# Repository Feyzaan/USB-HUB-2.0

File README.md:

# GL850G + TPS2044B USB Hub — Validation Board

A self-powered, 4-port USB 2.0 hub PCB built to validate independent per-port power switching and fault isolation before use in a larger project. Each downstream port can be individually enabled, current-limited, and fault-reported — a short or overcurrent event on one port never affects the others.

## Overview

Most low-cost USB hubs share power switching across all ports in a single "gang" — one fault trips every port at once. This board is designed the other way: each port has its own dedicated enable and fault-report line, driven by a hub controller running in **individual power mode**, with the actual current-limiting handled by a separate quad power-distribution switch.

This board exists purely to validate that architecture in isolation — no other subsystems, no assumptions carried over from a datasheet reference circuit without independent verification.

## Key Features

- **Independent per-port power switching** — each of the 4 downstream ports has its own enable/fault signal pair, not a shared gang-mode circuit
- **Active overcurrent protection** — a fault on one port trips only that port's power channel; the remaining ports continue operating normally
- **Self-powered architecture** — the hub sources its own downstream power rather than drawing everything from the host's USB port budget
- **Reverse-current protection** — a P-channel MOSFET on the USB-C input blocks the board's local supply from backfeeding into the host
- **USB Type-C current advertisement** — CC-line resistors advertise 1.5 A to the host instead of the USB 2.0 default of 500 mA, using passive resistors only (no PD controller)
- **Per-port status indication** — dual-color LEDs report each port's connection/fault state
- **Independent, isolated crystal oscillators** — the hub controller and any downstream logic run on separate, dedicated clock sources

## Hardware

| Function | Part |
|---|---|
| USB hub controller | Genesys Logic GL850G-MNG21 (LQFP48, individual power mode) |
| Power distribution switch | Texas Instruments TPS2044BDR (quad, independently current-limited channels) |
| Reverse-current blocking | SI2301 P-channel MOSFET |
| Host connector | USB-C (16-pin, reversible) |
| Downstream connectors | 4× USB-A |
| Status indication | Dual-color (green/amber) LEDs, one per port |

## Design Notes

- The hub controller's power-on strap pins configure port count, power-switch polarity, and per-port removable/non-removable status; several of these pins double as status-LED drivers after the strap window closes, requiring careful resistor sizing so the two functions don't interfere with each other.
- Overcurrent-report lines are open-drain and require external pull-ups — this is easy to miss if relying on a symbol's default connections rather than the manufacturer's application circuit.
- Reset sensing is derived from the raw, upstream USB VBUS rail (ahead of the reverse-blocking MOSFET) rather than the board's own regulated rail, so a cable disconnect is detected immediately rather than after the local bulk capacitance discharges.

## Status

Schematic complete and cross-checked pin-by-pin against manufacturer datasheets. PCB fabrication in progress.

## Gallery

**3D render**

**Copper layers**

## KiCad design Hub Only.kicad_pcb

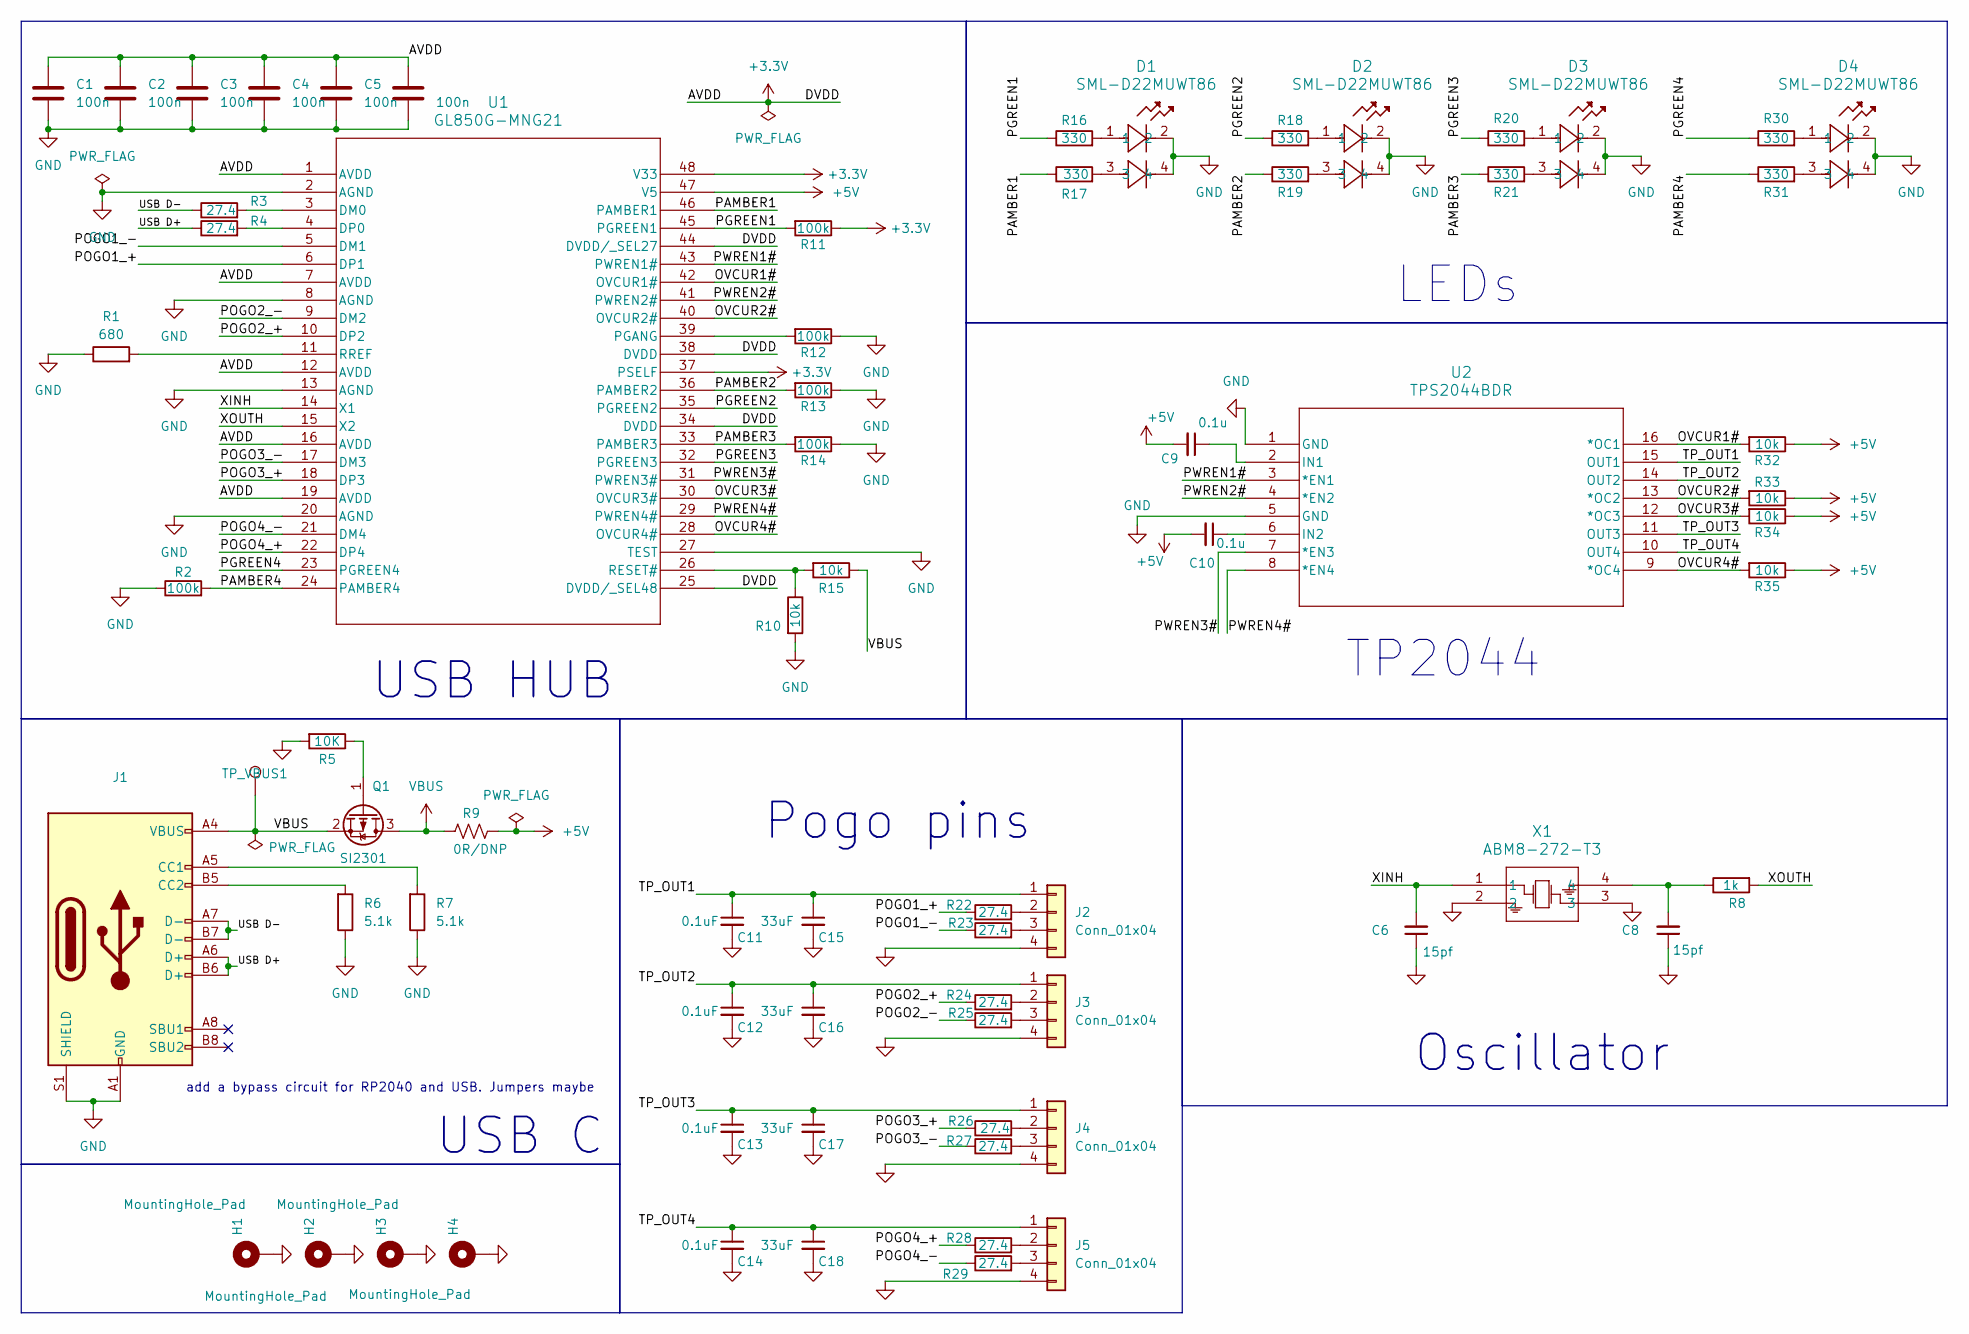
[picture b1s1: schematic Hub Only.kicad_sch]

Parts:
C1, C2, C3, C4, C5, C7: 100n; C_0603_1608Metric
C6, C8: 15pf; C_0603_1608Metric
C9, C10: 0.1u; C_0603_1608Metric
C11, C12, C13, C14: 0.1uF; C_0603_1608Metric
C15, C16, C17, C18: 33uF; C_0603_1608Metric
D1, D2, D3, D4: SML-D22MUWT86; LED_SML-D22_ROM
H1, H2, H3, H4: MountingHole_Pad; MountingHole_2.2mm_M2_DIN965_Pad
J1: USB_C_Receptacle_XKB_U262-16XN-4BVC11
J2, J3, J4, J5: Conn_01x04; USB_A_Molex_67643_Horizontal
Q1: SI2301; SOT-23
R1: 680; R_0603_1608Metric_Pad0.98x0.95mm_HandSolder
R2, R11, R12, R13, R14: 100k; R_0603_1608Metric_Pad0.98x0.95mm_HandSolder
R3, R4, R22, R23, R24, R25, R26, R27, R28, R29: 27.4; R_0603_1608Metric_Pad0.98x0.95mm_HandSolder
R5: 10K; R_0603_1608Metric_Pad0.98x0.95mm_HandSolder
R6, R7: 5.1k; R_0603_1608Metric
R8: 1k; R_0603_1608Metric
R9: 0R/DNP; R_0603_1608Metric
R10, R15, R32, R33, R34, R35: 10k; R_0603_1608Metric_Pad0.98x0.95mm_HandSolder
R16, R17, R18, R19, R20, R21, R30, R31: 330; R_0603_1608Metric_Pad0.98x0.95mm_HandSolder
TP_VBUS1: TestPoint; TestPoint_Pad_D1.0mm
U1: GL850G-MNG21; QFN48_GL850G_7x7-0P5_GEN
U2: TPS2044BDR; D16
X1: ABM8-272-T3; ABM8-272-T3_ABR

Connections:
+3.3V: C1.2, C2.2, C3.2, C4.2, C5.2, C7.2, R11.1, U1.1 (AVDD), U1.7 (AVDD), U1.12 (AVDD), U1.16 (AVDD), U1.19 (AVDD), U1.25 (DVDD/_SEL48), U1.34 (DVDD), U1.37 (PSELF), U1.38 (DVDD), U1.44 (DVDD/_SEL27), U1.48 (V33)
+5V: C9.2, C10.2, R9.2, R32.1, R33.1, R34.1, R35.1, U1.47 (V5)
/OVCUR1#: R32.2, U1.42 (OVCUR1#), U2.16 (*OC1)
/OVCUR2#: R33.2, U1.40 (OVCUR2#), U2.13 (*OC2)
/OVCUR3#: R34.2, U1.30 (OVCUR3#), U2.12 (*OC3)
/OVCUR4#: R35.2, U1.28 (OVCUR4#), U2.9 (*OC4)
/PAMBER1: R17.1, U1.46 (PAMBER1)
/PAMBER2: R13.2, R19.1, U1.36 (PAMBER2)
/PAMBER3: R14.2, R21.1, U1.33 (PAMBER3)
/PAMBER4: R2.2, R31.1, U1.24 (PAMBER4)
/PGREEN1: R11.2, R16.1, U1.45 (PGREEN1)
/PGREEN2: R18.1, U1.35 (PGREEN2)
/PGREEN3: R20.1, U1.32 (PGREEN3)
/PGREEN4: R30.1, U1.23 (PGREEN4)
/POGO1_+: R22.1, U1.6 (DP1)
/POGO1_-: R23.1, U1.5 (DM1)
/POGO2_+: R24.1, U1.10 (DP2)
/POGO2_-: R25.1, U1.9 (DM2)
/POGO3_+: R26.1, U1.18 (DP3)
/POGO3_-: R27.1, U1.17 (DM3)
/POGO4_+: R28.1, U1.22 (DP4)
/POGO4_-: R29.1, U1.21 (DM4)
/PWREN1#: U1.43 (PWREN1#), U2.3 (*EN1)
/PWREN2#: U1.41 (PWREN2#), U2.4 (*EN2)
/PWREN3#: U1.31 (PWREN3#), U2.7 (*EN3)
/PWREN4#: U1.29 (PWREN4#), U2.8 (*EN4)
/TP_OUT1: C11.1, C15.1, J2.1, U2.15 (OUT1)
/TP_OUT2: C12.1, C16.1, J3.1, U2.14 (OUT2)
/TP_OUT3: C13.1, C17.1, J4.1, U2.11 (OUT3)
/TP_OUT4: C14.1, C18.1, J5.1, U2.10 (OUT4)
/USB D+: J1.A6 (D+), J1.B6 (D+), R4.1
/USB D-: J1.A7 (D-), J1.B7 (D-), R3.1
/XINH: C6.2, U1.14 (X1), X1.1
/XOUTH: R8.1, U1.15 (X2)
GND: C1.1, C2.1, C3.1, C4.1, C5.1, C6.1, C7.1, C8.1, C11.2, C12.2, C13.2, C14.2, C15.2, C16.2, C17.2, C18.2, D1.2, D1.4, D2.2, D2.4, D3.2, D3.4, D4.2, D4.4, H1.1, H2.1, H3.1, H4.1, J1.A1 (GND), J1.A12 (GND), J1.B1 (GND), J1.B12 (GND), J1.S1 (SHIELD), J2.4, J3.4, J4.4, J5.4, R1.1, R2.1, R5.2, R6.2, R7.2, R10.2, R12.1, R13.1, R14.1, U1.2 (AGND), U1.8 (AGND), U1.13 (AGND), U1.20 (AGND), U1.27 (TEST), U2.1 (GND), U2.5 (GND), X1.2, X1.3
unnamed: C8.2, R8.2, X1.4
unnamed: D1.1, R16.2
unnamed: D1.3, R17.2
unnamed: D2.1, R18.2
unnamed: D2.3, R19.2
unnamed: D3.1, R20.2
unnamed: D3.3, R21.2
unnamed: D4.1, R30.2
unnamed: D4.3, R31.2
unnamed: J1.A5 (CC1), R7.1
unnamed: J1.B5 (CC2), R6.1
unnamed: J2.2, R22.2
unnamed: J2.3, R23.2
unnamed: J3.2, R24.2
unnamed: J3.3, R25.2
unnamed: J4.2, R26.2
unnamed: J4.3, R27.2
unnamed: J5.2, R28.2
unnamed: J5.3, R29.2
unnamed: Q1.1 (G), R5.1
unnamed: R3.2, U1.3 (DM0)
unnamed: R4.2, U1.4 (DP0)
unnamed: R12.2, U1.39 (PGANG)
unnamed: R10.1, R15.2, U1.26 (RESET#)
unnamed: R1.2, U1.11 (RREF)
unnamed: C9.1, U2.2 (IN1)
unnamed: C10.1, U2.6 (IN2)
VBUS: J1.A4 (VBUS), J1.A9 (VBUS), J1.B4 (VBUS), J1.B9 (VBUS), Q1.2 (S), Q1.3 (D), R9.1, R15.1, TP_VBUS1.1

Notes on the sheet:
Oscillator
USB C
USB HUB
LEDs
add a bypass circuit for RP2040 and USB. Jumpers maybe
TP2044
Pogo pins

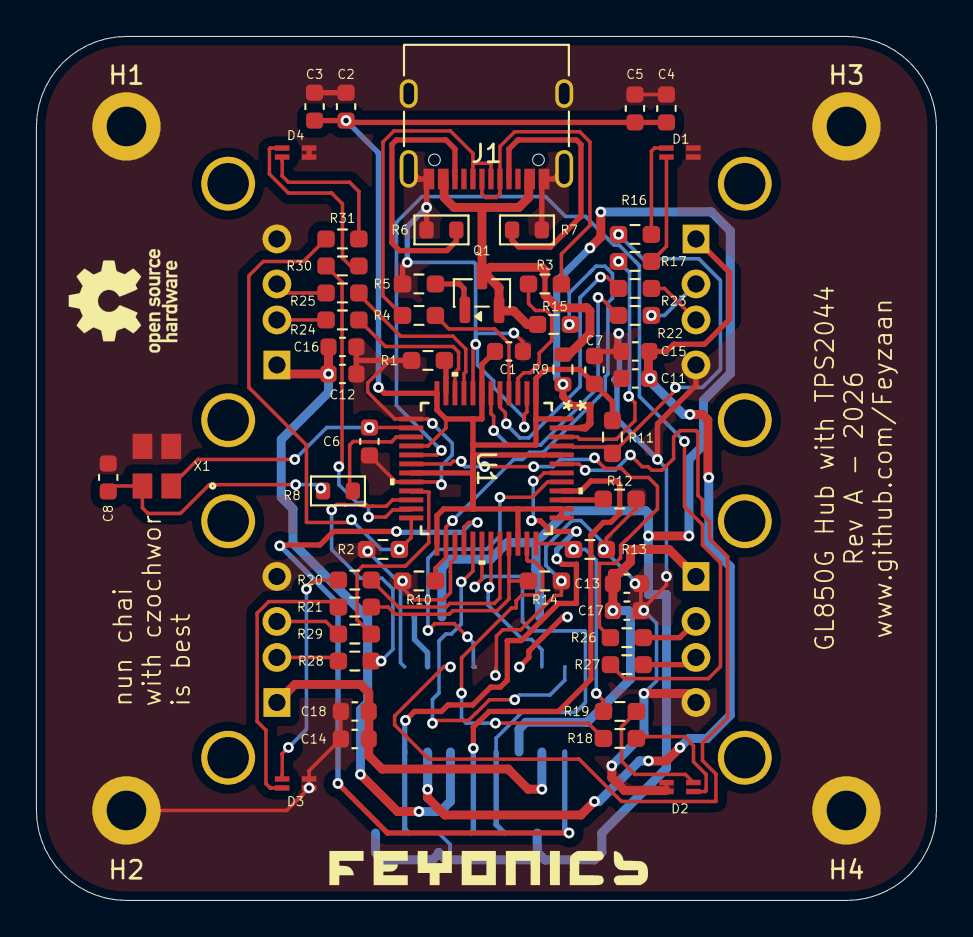
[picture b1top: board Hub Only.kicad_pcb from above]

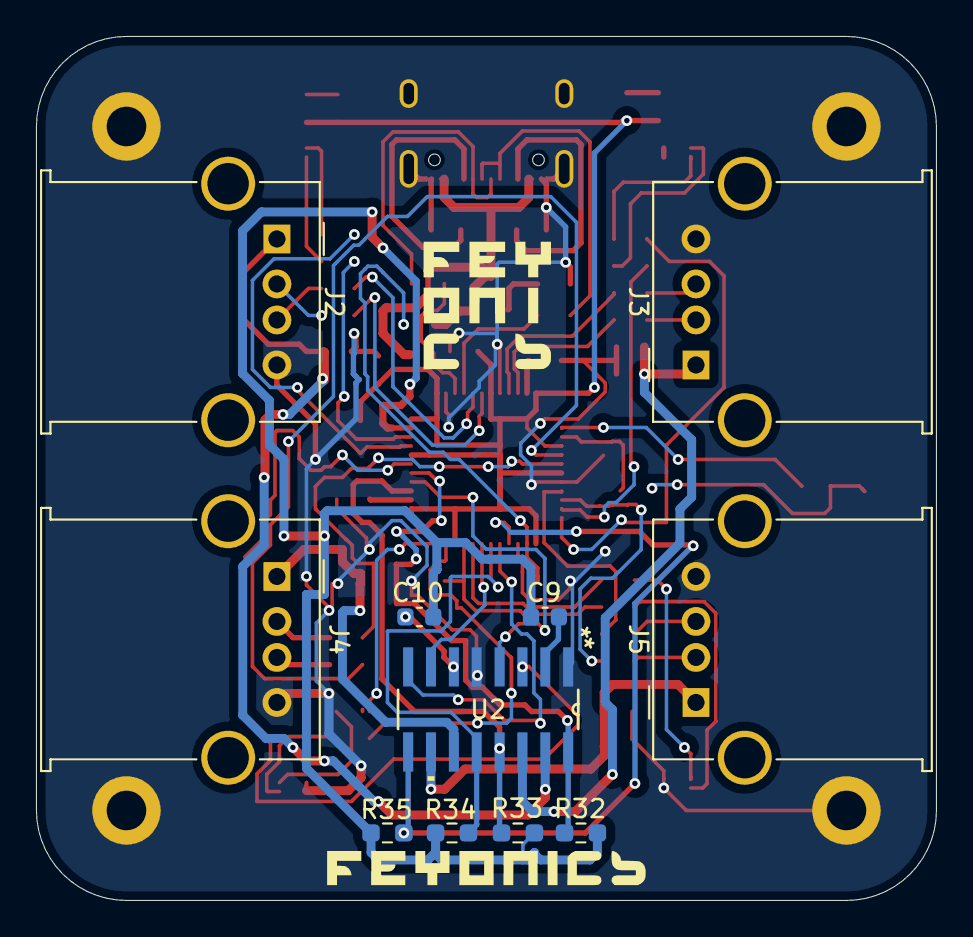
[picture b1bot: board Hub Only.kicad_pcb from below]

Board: 2 copper layers, 50.0 x 48.0 mm, 70 parts (11 on the bottom side), 63 nets.
